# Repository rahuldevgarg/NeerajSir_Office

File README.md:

# NeerajSir_Office
This Repo is intended for Neeraj Sir's Office Automatiom

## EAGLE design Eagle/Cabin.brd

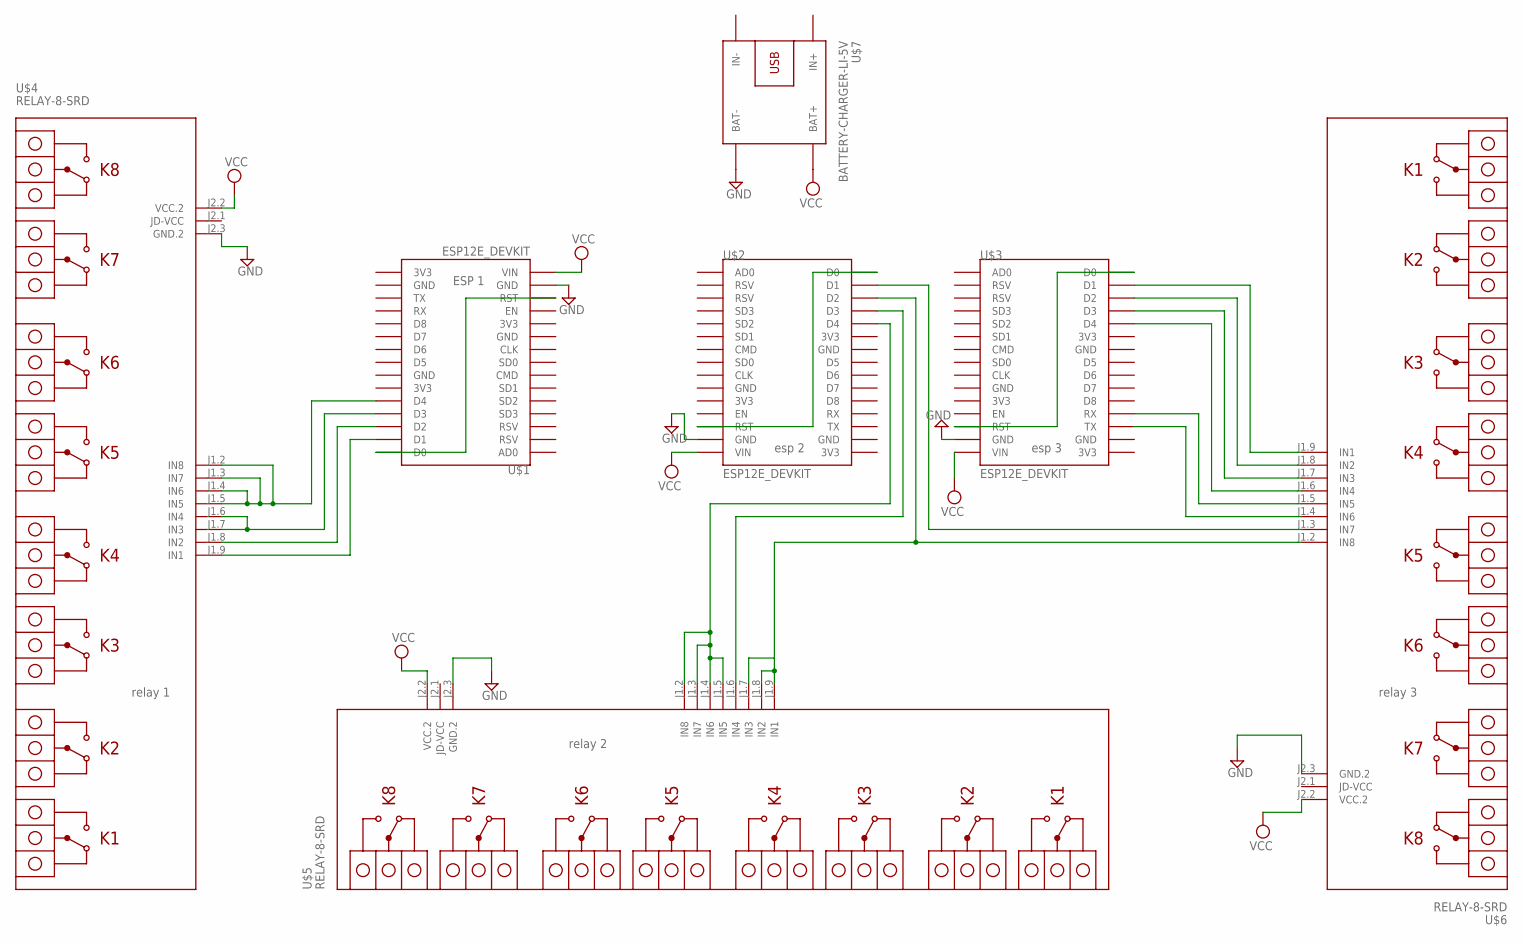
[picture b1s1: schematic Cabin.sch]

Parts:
U$1, U$2, U$3: ESP12E_DEVKIT
U$4, U$5, U$6: RELAY-8-SRD
U$7: BATTERY-CHARGER-LI-5V

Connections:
GND: U$1.GND@1 (GND), U$2.GND@1 (GND), U$3.GND@1 (GND), U$4.J2.3 (GND.2), U$5.J2.3 (GND.2), U$6.J2.3 (GND.2), U$7.BAT-
unnamed: U$2.D0, U$2.RST
unnamed: U$1.D0, U$1.RST
unnamed: U$2.D1, U$6.J1.3 (IN7)
unnamed: U$3.D0, U$3.RST
unnamed: U$1.D1, U$4.J1.9 (IN1)
unnamed: U$1.D2, U$4.J1.8 (IN2)
unnamed: U$1.D3, U$4.J1.6 (IN4), U$4.J1.7 (IN3)
unnamed: U$1.D4, U$4.J1.2 (IN8), U$4.J1.3 (IN7), U$4.J1.4 (IN6), U$4.J1.5 (IN5)
unnamed: U$3.D1, U$6.J1.9 (IN1)
unnamed: U$3.D2, U$6.J1.8 (IN2)
unnamed: U$3.D3, U$6.J1.7 (IN3)
unnamed: U$3.D4, U$6.J1.6 (IN4)
unnamed: U$3.RX, U$6.J1.5 (IN5)
unnamed: U$3.TX, U$6.J1.4 (IN6)
unnamed: U$2.D2, U$5.J1.7 (IN3), U$5.J1.8 (IN2), U$5.J1.9 (IN1), U$6.J1.2 (IN8)
unnamed: U$2.D3, U$5.J1.6 (IN4)
unnamed: U$2.D4, U$5.J1.2 (IN8), U$5.J1.3 (IN7), U$5.J1.4 (IN6), U$5.J1.5 (IN5)
VCC: U$1.VIN, U$2.VIN, U$3.VIN, U$4.J2.2 (VCC.2), U$5.J2.2 (VCC.2), U$6.J2.2 (VCC.2), U$7.BAT+

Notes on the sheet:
ESP 1
esp 2
esp 3
relay 1
relay 2
relay 3

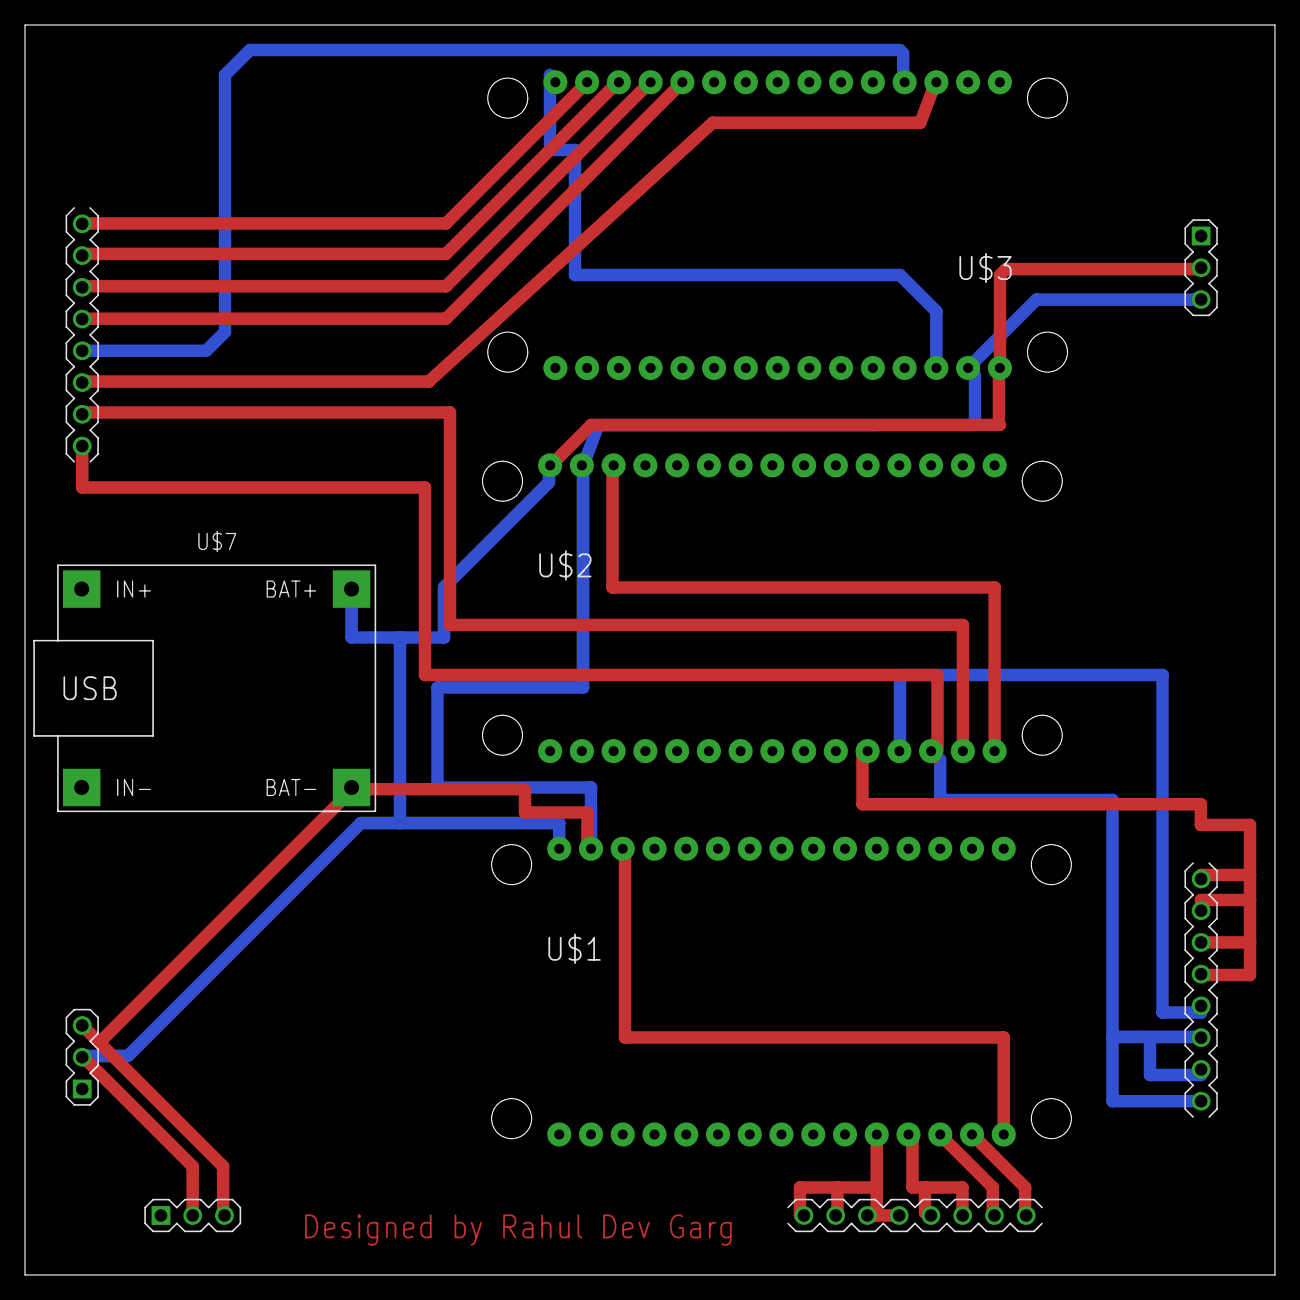
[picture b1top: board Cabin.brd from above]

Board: 2 copper layers, 100.0 x 100.0 mm, 7 parts (0 on the bottom side), 19 nets.

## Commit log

2019-04-21 Initial WhiteSource configuration file
2019-04-21 ino files
2019-04-21 eagle files

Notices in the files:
parts and their libraries:
diy-modules: Released under the Creative Commons Attribution 4.0 International License: http://creativecommons.org/licenses/by/4.0
